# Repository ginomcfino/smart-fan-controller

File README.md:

# Smart Cabinet Fan Controller

A dual-fan controller design with temperature inputs, tachometer conditioning, a hardware overtemperature alarm, and manual override.

**Status:** CAD design study

This is my manually developed circuit and PCB design. Component libraries, manufacturer models, and other supplied assets retain their original attribution.

- [Hardware source](hardware/): schematics, PCB, project, and required local libraries.
- [Schematic PDF](exports/schematic.pdf): all schematic sheets.
- [Visual guide](docs/visuals.md): labeled board and schematic views.
- [Check notes](docs/checks/README.md): packaging checks and current automated-check results.

Open `hardware/Smart_Cabinet_Fan.kicad_pro` with KiCad 10 and its standard symbol, footprint, and 3D model libraries.

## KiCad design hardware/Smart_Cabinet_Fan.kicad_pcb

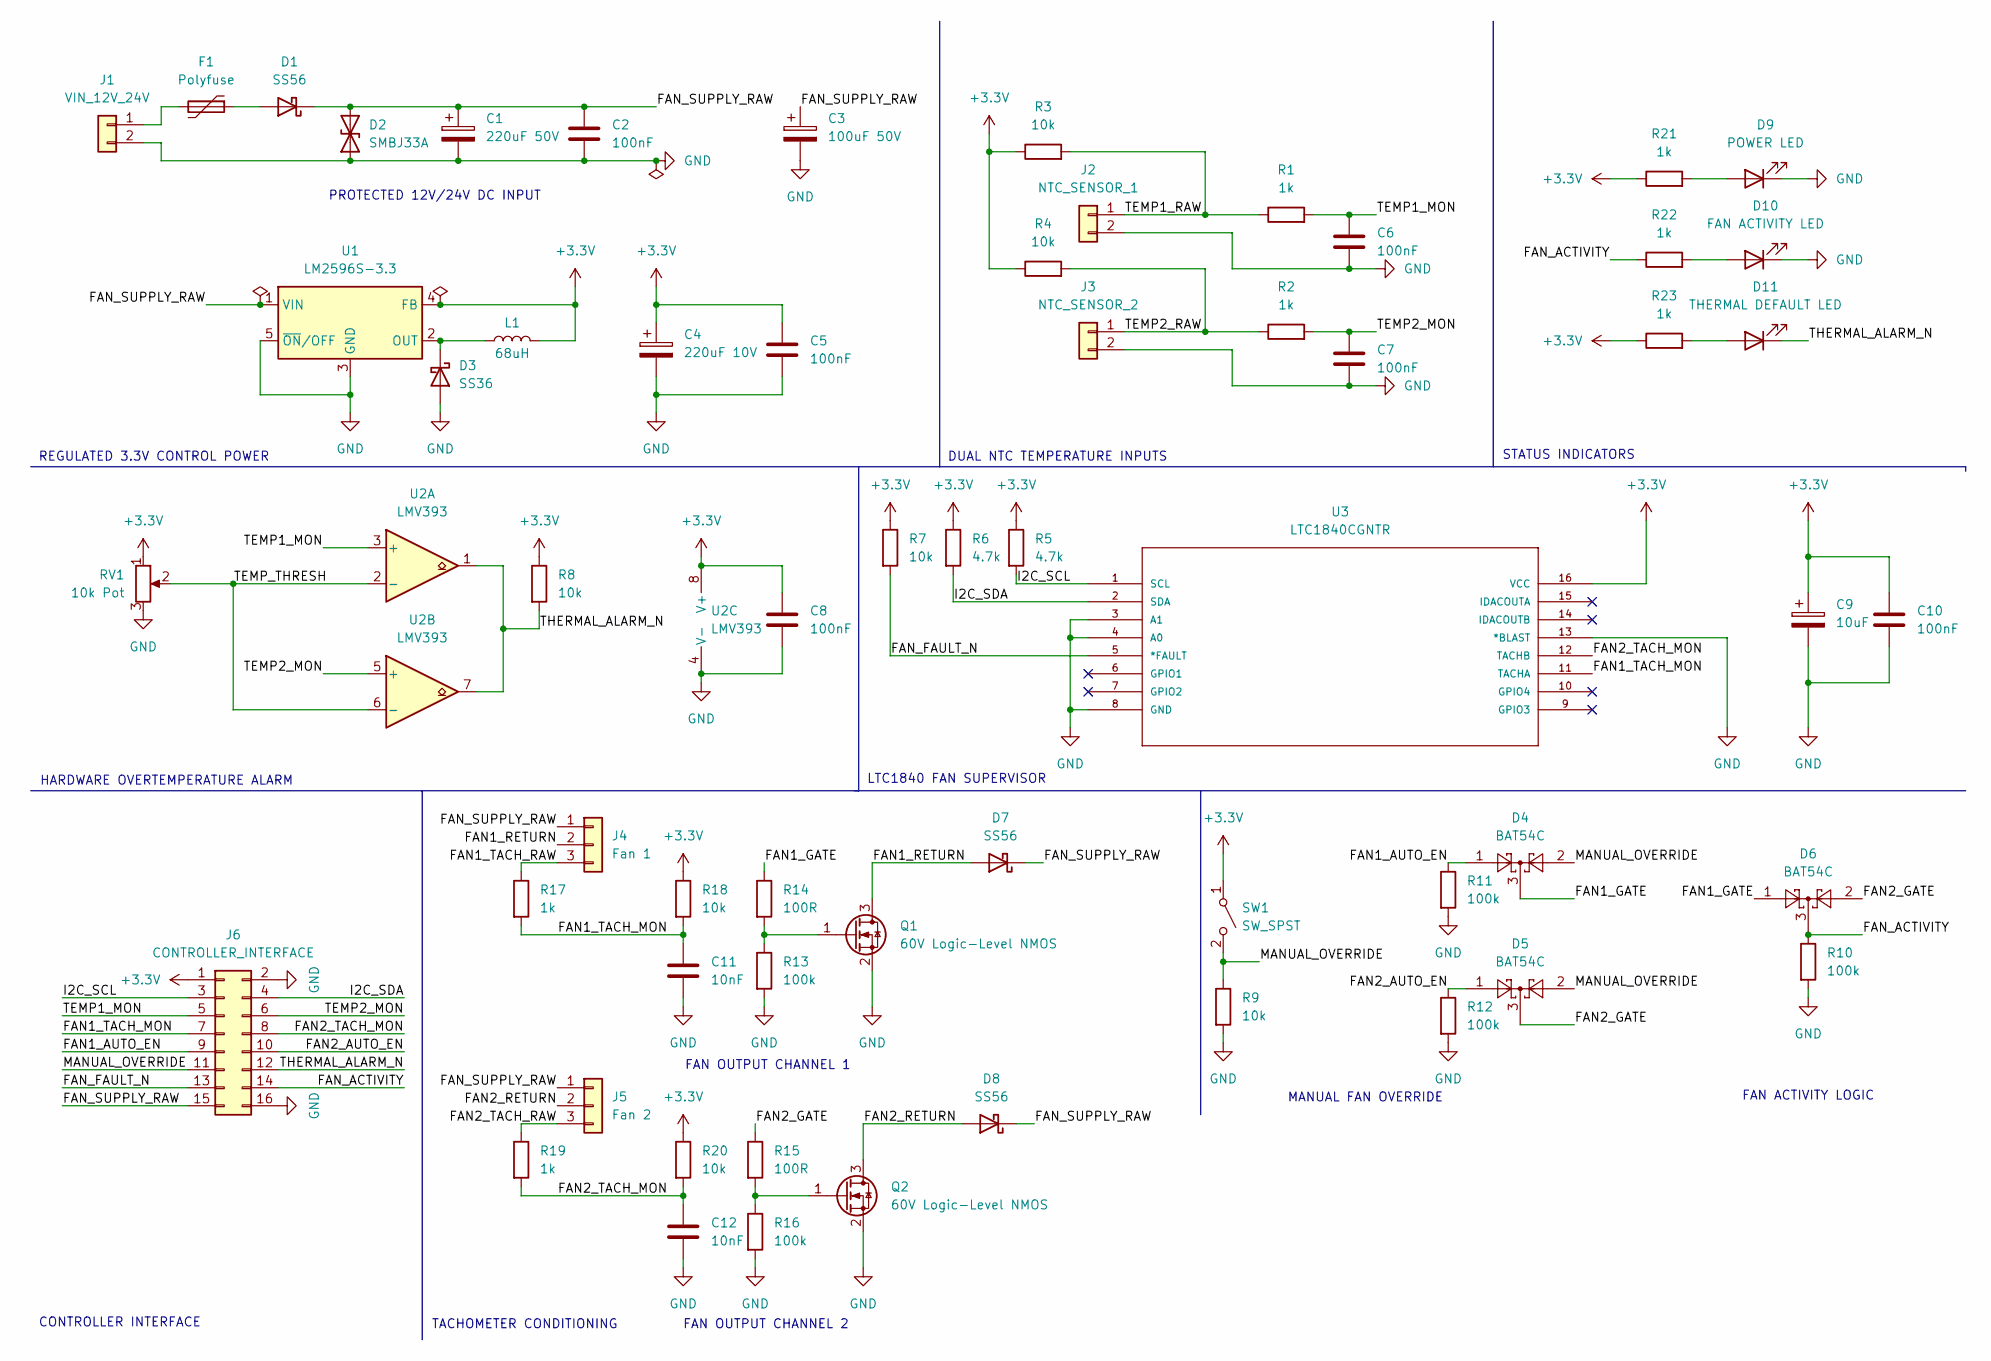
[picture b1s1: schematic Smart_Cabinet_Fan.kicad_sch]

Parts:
C1: 220uF 50V; CP_Elec_10x12.5
C2, C5, C6, C7, C8, C10: 100nF; C_0805_2012Metric
C3: 100uF 50V; CP_Elec_10x10
C4: 220uF 10V; CP_Elec_10x7.7
C9: 10uF; CP_Elec_5x5.4
C11, C12: 10nF; C_0805_2012Metric
D1, D7, D8: SS56; D_SMB
D2: SMBJ33A; D_SMB
D3: SS36; D_SMA
D4, D5, D6: BAT54C; SOT-23
D9: POWER LED; LED_0805_2012Metric
D10: FAN ACTIVITY LED; LED_0805_2012Metric
D11: THERMAL DEFAULT LED; LED_0805_2012Metric
F1: Polyfuse; Fuse_1812_4532Metric
J1: VIN_12V_24V; TerminalBlock_Phoenix_MKDS-1,5-2_1x02_P5.00mm_Horizontal
J2: NTC_SENSOR_1; TerminalBlock_Phoenix_MKDS-1,5-2_1x02_P5.00mm_Horizontal
J3: NTC_SENSOR_2; TerminalBlock_Phoenix_MKDS-1,5-2_1x02_P5.00mm_Horizontal
J4: Fan 1; PinHeader_1x03_P2.54mm_Horizontal
J5: Fan 2; PinHeader_1x03_P2.54mm_Horizontal
J6: CONTROLLER_INTERFACE; PinHeader_2x08_P2.54mm_Horizontal
L1: 68uH; L_Bourns_SRR1260
Q1, Q2: 60V Logic-Level NMOS; TO-252-3_TabPin2
R1, R2, R17, R19, R21, R22, R23: 1k; R_0805_2012Metric
R3, R4, R7, R8, R9, R18, R20: 10k; R_0805_2012Metric
R5, R6: 4.7k; R_0805_2012Metric
R10, R11, R12, R13, R16: 100k; R_0805_2012Metric
R14, R15: 100R; R_0805_2012Metric
RV1: 10k Pot; Potentiometer_Bourns_3296W_Vertical
SW1: SW_SPST; SW_DIP_SPSTx01_Slide_9.78x4.72mm_W7.62mm_P2.54mm
U1: LM2596S-3.3; TO-263-5_TabPin3
U2: LMV393; SOIC-8_3.9x4.9mm_P1.27mm
U3: LTC1840CGNTR; SSOP-16_3.9x4.9mm_P0.635mm; MANUFACTURER_PART_NUMBER ltc1840cgn#tr

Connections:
+3.3V: C4.1, C5.1, C8.1, C9.1, C10.1, J6.1, L1.2, R3.1, R4.1, R5.1, R6.1, R7.1, R8.1, R18.1, R20.1, R21.1, R23.1, RV1.1, SW1.1 (A), U1.4 (FB), U2.8 (V+), U3.16 (VCC)
/FAN1_AUTO_EN: D4.1, J6.9, R11.1
/FAN1_GATE: D4.3, D6.1, R14.1
/FAN1_RETURN: D7.2 (A), J4.2, Q1.3 (D)
/FAN1_TACH_MON: C11.1, J6.7, R17.2, R18.2, U3.11 (TACHA)
/FAN1_TACH_RAW: J4.3, R17.1
/FAN2_AUTO_EN: D5.1, J6.10, R12.1
/FAN2_GATE: D5.3, D6.2, R15.1
/FAN2_RETURN: D8.2 (A), J5.2, Q2.3 (D)
/FAN2_TACH_MON: C12.1, J6.8, R19.2, R20.2, U3.12 (TACHB)
/FAN2_TACH_RAW: J5.3, R19.1
/FAN_ACTIVITY: D6.3, J6.14, R10.1, R22.1
/FAN_FAULT_N: J6.13, R7.2, U3.5 (*FAULT)
/FAN_SUPPLY_RAW: C1.1, C2.1, C3.1, D1.1 (K), D2.2 (A2), D7.1 (K), D8.1 (K), J4.1, J5.1, J6.15, U1.1 (VIN)
/I2C_SCL: J6.3, R5.2, U3.1 (SCL)
/I2C_SDA: J6.4, R6.2, U3.2 (SDA)
/MANUAL_OVERRIDE: D4.2, D5.2, J6.11, R9.1, SW1.2 (B)
/TEMP1_MON: C6.1, J6.5, R1.2, U2.3 (+)
/TEMP1_RAW: J2.1, R1.1, R3.2
/TEMP2_MON: C7.1, J6.6, R2.2, U2.5 (+)
/TEMP2_RAW: J3.1, R2.1, R4.2
/TEMP_THRESH: RV1.2, U2.2 (-), U2.6 (-)
/THERMAL_ALARM_N: D11.1 (K), J6.12, R8.2, U2.1, U2.7
GND: C1.2, C2.2, C3.2, C4.2, C5.2, C6.2, C7.2, C8.2, C9.2, C10.2, C11.2, C12.2, D2.1 (A1), D3.2 (A), D9.1 (K), D10.1 (K), J1.2, J2.2, J3.2, J6.2, J6.16, Q1.2 (S), Q2.2 (S), R9.2, R10.2, R11.2, R12.2, R13.2, R16.2, RV1.3, U1.3 (GND), U1.5 (~ON/OFF), U2.4 (V-), U3.3 (A1), U3.4 (A0), U3.8 (GND), U3.13 (*BLAST)
unnamed: D1.2 (A), F1.1
unnamed: D3.1 (K), L1.1, U1.2 (OUT)
unnamed: D9.2 (A), R21.2
unnamed: D10.2 (A), R22.2
unnamed: D11.2 (A), R23.2
unnamed: F1.2, J1.1
unnamed: Q1.1 (G), R13.1, R14.2
unnamed: Q2.1 (G), R15.2, R16.1

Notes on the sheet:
FAN ACTIVITY LOGIC
FAN OUTPUT CHANNEL 1
CONTROLLER INTERFACE
TACHOMETER CONDITIONING
DUAL NTC TEMPERATURE INPUTS
LTC1840 FAN SUPERVISOR
FAN OUTPUT CHANNEL 2
MANUAL FAN OVERRIDE
HARDWARE OVERTEMPERATURE ALARM
PROTECTED 12V/24V DC INPUT
STATUS INDICATORS
REGULATED 3.3V CONTROL POWER

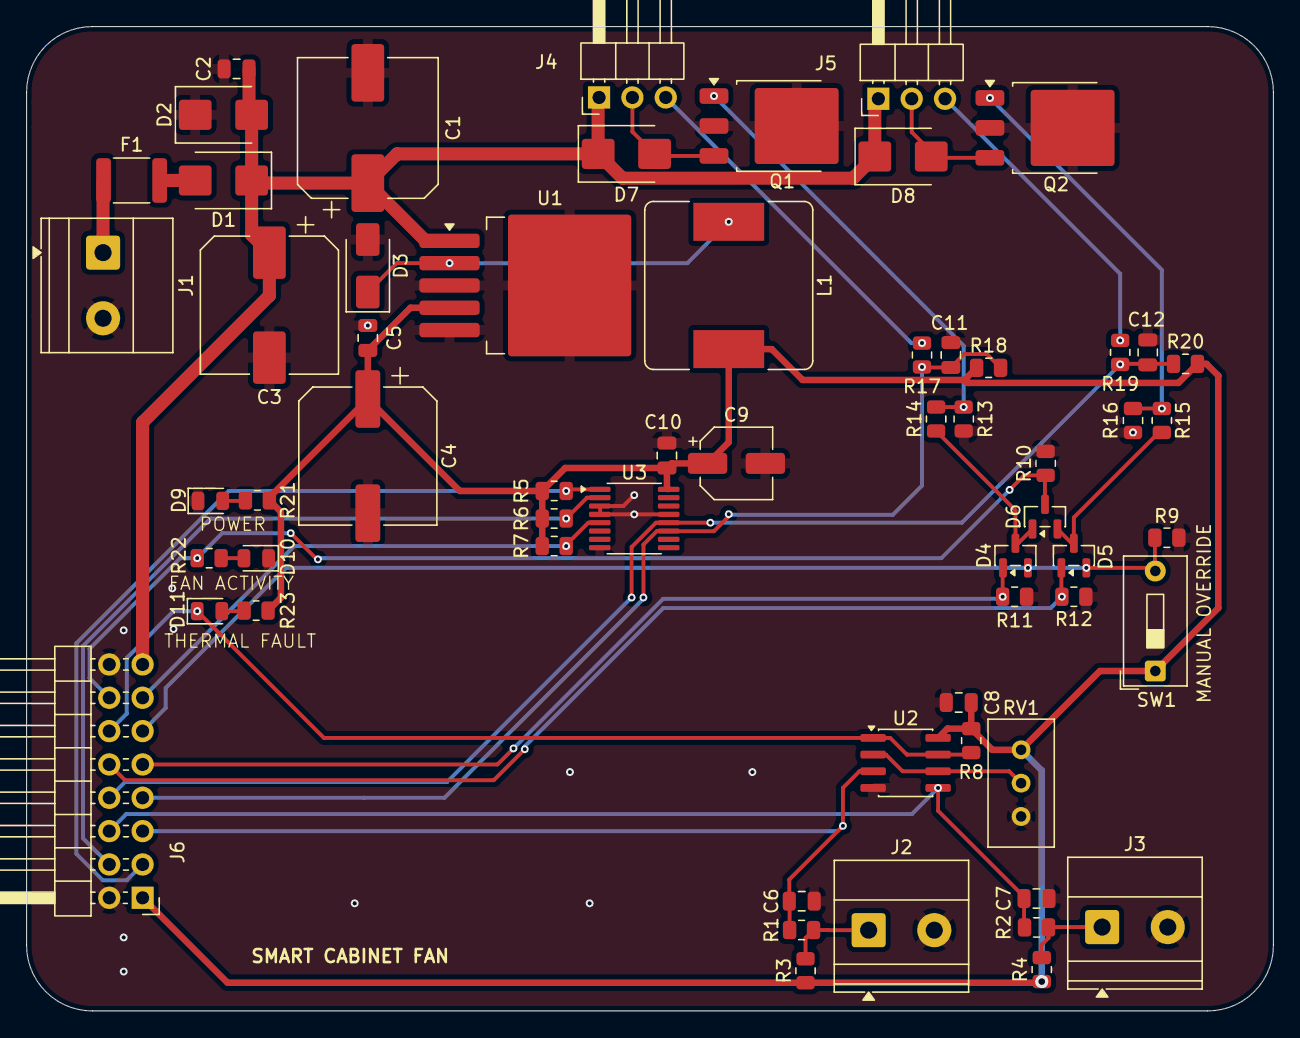
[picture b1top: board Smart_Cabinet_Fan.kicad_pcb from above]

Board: 2 copper layers, 95.0 x 75.0 mm, 61 parts (0 on the bottom side), 32 nets.
